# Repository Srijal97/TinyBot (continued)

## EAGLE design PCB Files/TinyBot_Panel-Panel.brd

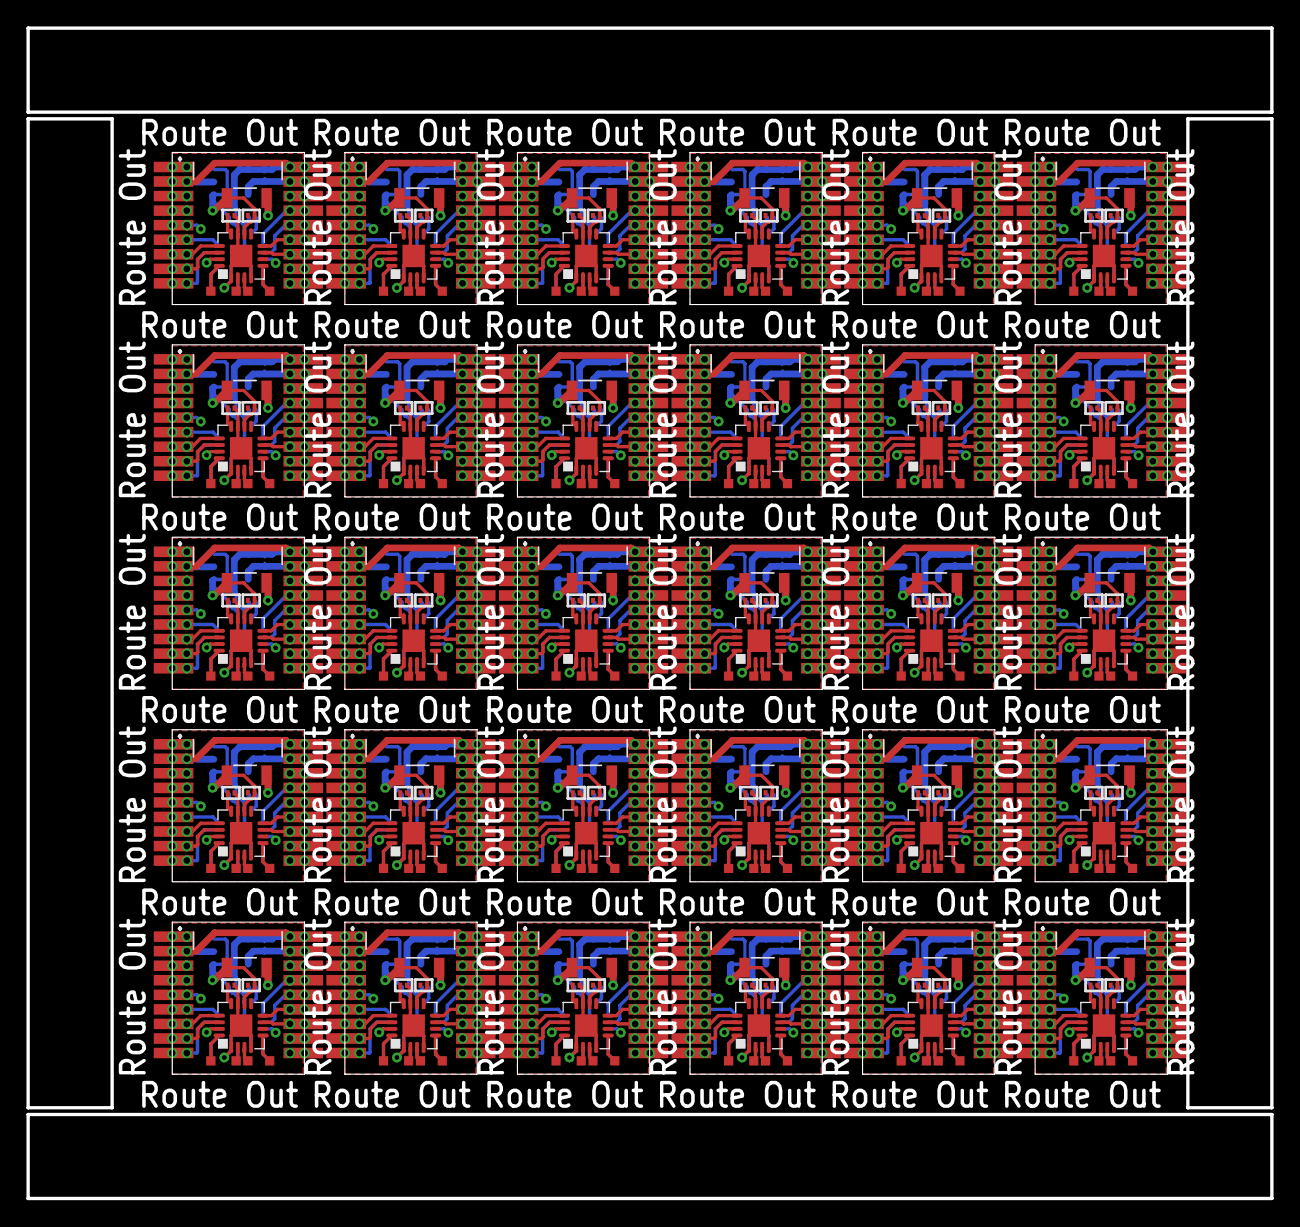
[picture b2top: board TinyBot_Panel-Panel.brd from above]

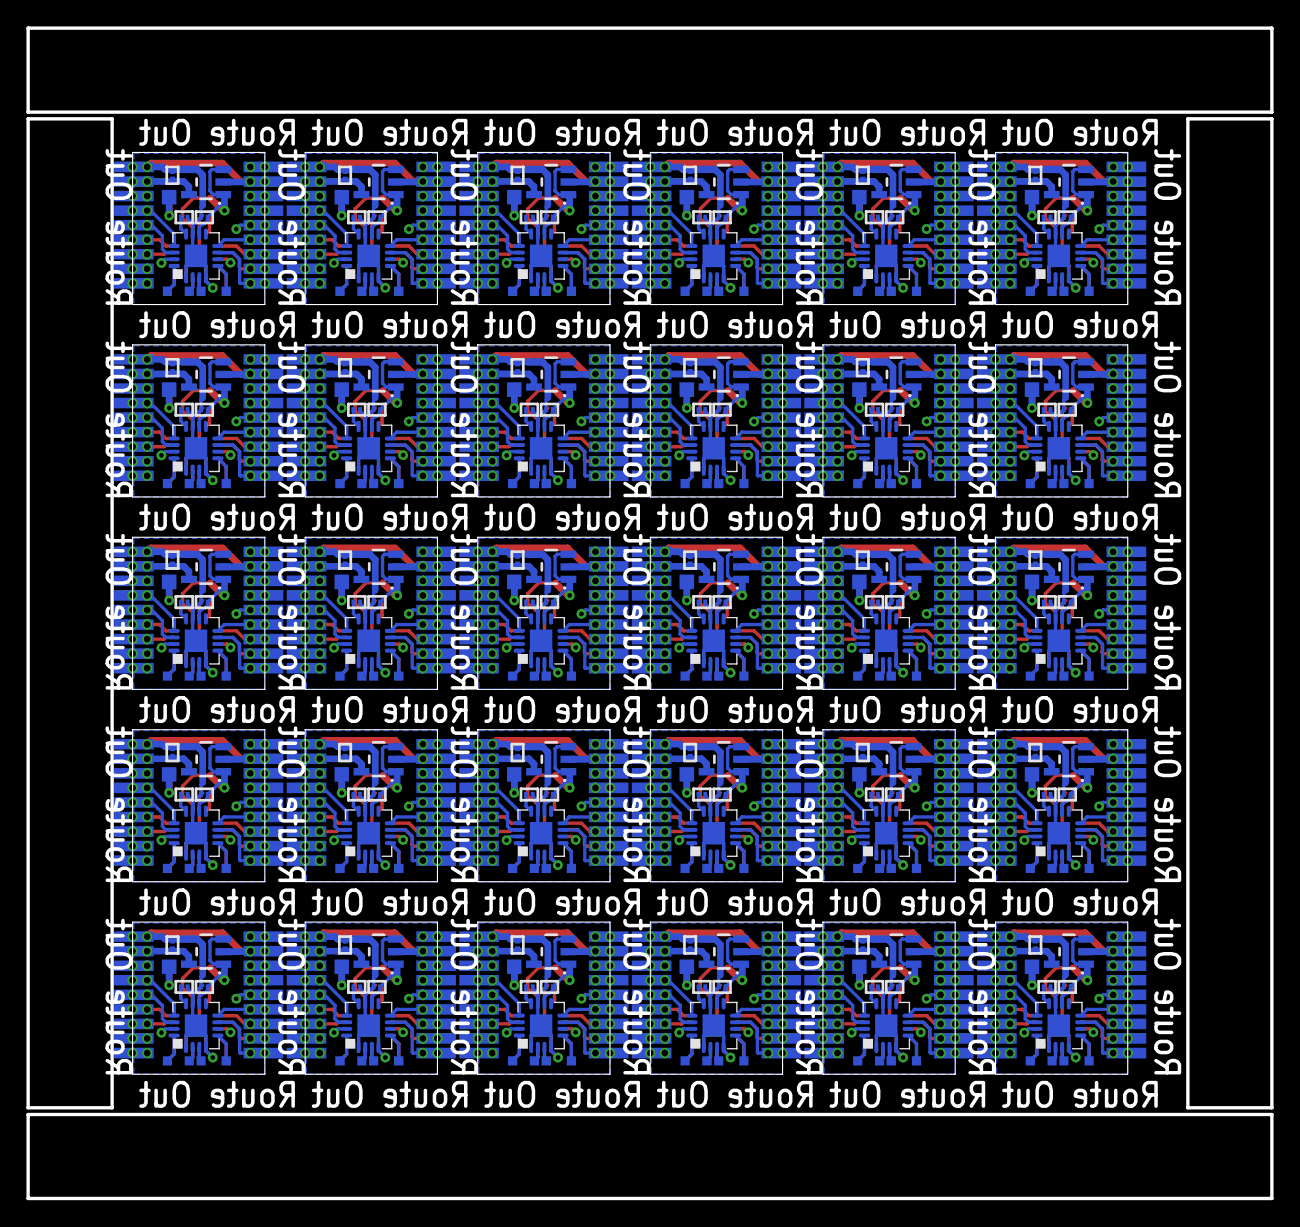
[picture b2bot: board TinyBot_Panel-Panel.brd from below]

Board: 2 copper layers, 94.0 x 88.5 mm, 570 parts (300 on the bottom side), 690 nets.

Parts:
C1, C2, C3, C4, C5, C6, C7, C8, C9, C10, C11, C12, C13, C14, C15, C16, C17, C18, C19, C20, C21, C22, C23, C24, C25, C26, C27, C28, C29, C30, C31, C32, C33, C34, C35, C36, C37, C38, C39, C40, C41, C42, C43, C44, C45, C46, C47, C48, C49, C50, C51, C52, C53, C54, C55, C56, C57, C58, C59, C60, C61, C62, C63, C64, C65, C66, C67, C68, C69, C70, C71, C72, C73, C74, C75, C76, C77, C78, C79, C80, C81, C82, C83, C84, C85, C86, C87, C88, C89, C90, C91, C92, C93, C94, C95, C96, C97, C98, C99, C100, C101, C102, C103, C104, C105, C106, C107, C108, C109, C110, C111, C112, C113, C114, C115, C116, C117, C118, C119, C120, C121, C122, C123, C124, C125, C126, C127, C128, C129, C130, C131, C132, C133, C134, C135, C136, C137, C138, C139, C140, C141, C142, C143, C144, C145, C146, C147, C148, C149, C150: C0201
LIPO_IN, LIPO_IN1, LIPO_IN2, LIPO_IN3, LIPO_IN4, LIPO_IN5, LIPO_IN6, LIPO_IN7, LIPO_IN8, LIPO_IN9, LIPO_IN10, LIPO_IN11, LIPO_IN12, LIPO_IN13, LIPO_IN14, LIPO_IN15, LIPO_IN16, LIPO_IN17, LIPO_IN18, LIPO_IN19, LIPO_IN20, LIPO_IN21, LIPO_IN22, LIPO_IN23, LIPO_IN24, LIPO_IN25, LIPO_IN26, LIPO_IN27, LIPO_IN28, LIPO_IN29: TPTP11SQ; TP11SQ
TP1, TP2, TP3, TP4, TP5, TP6, TP7, TP8, TP9, TP10, TP11, TP12, TP13, TP14, TP15, TP16, TP17, TP18, TP19, TP20, TP21, TP22, TP23, TP24, TP25, TP26, TP27, TP28, TP29, TP30, TP31, TP32, TP33, TP34, TP35, TP36, TP37, TP38, TP39, TP40, TP41, TP42, TP43, TP44, TP45, TP46, TP47, TP48, TP49, TP50, TP51, TP52, TP53, TP54, TP55, TP56, TP57, TP58, TP59, TP60, TP61, TP62, TP63, TP64, TP65, TP66, TP67, TP68, TP69, TP70, TP71, TP72, TP73, TP74, TP75, TP76, TP77, TP78, TP79, TP80, TP81, TP82, TP83, TP84, TP85, TP86, TP87, TP88, TP89, TP90, TP91, TP92, TP93, TP94, TP95, TP96, TP97, TP98, TP99, TP100, TP101, TP102, TP103, TP104, TP105, TP106, TP107, TP108, TP109, TP110, TP111, TP112, TP113, TP114, TP115, TP116, TP117, TP118, TP119, TP120, TP121, TP122, TP123, TP124, TP125, TP126, TP127, TP128, TP129, TP130, TP131, TP132, TP133, TP134, TP135, TP136, TP137, TP138, TP139, TP140, TP141, TP142, TP143, TP144, TP145, TP146, TP147, TP148, TP149, TP150, TP151, TP152, TP153, TP154, TP155, TP156, TP157, TP158, TP159, TP160, TP161, TP162, TP163, TP164, TP165, TP166, TP167, TP168, TP169, TP170, TP171, TP172, TP173, TP174, TP175, TP176, TP177, TP178, TP179, TP180, TP181, TP182, TP183, TP184, TP185, TP186, TP187, TP188, TP189, TP190, TP191, TP192, TP193, TP194, TP195, TP196, TP197, TP198, TP199, TP200, TP201, TP202, TP203, TP204, TP205, TP206, TP207, TP208, TP209, TP210, TP211, TP212, TP213, TP214, TP215, TP216, TP217, TP218, TP219, TP220, TP221, TP222, TP223, TP224, TP225, TP226, TP227, TP228, TP229, TP230, TP231, TP232, TP233, TP234, TP235, TP236, TP237, TP238, TP239, TP240: TPTP07SQ; TP07SQ
U$1, U$2, U$9, U$15, U$21, U$26, U$31, U$36, U$41, U$46, U$51, U$56, U$61, U$66, U$71, U$76, U$81, U$86, U$91, U$96, U$101, U$106, U$111, U$116, U$121, U$126, U$131, U$136, U$141, U$146: ESP01F
U$3, U$5, U$10, U$17, U$22, U$27, U$32, U$37, U$42, U$47, U$52, U$57, U$62, U$67, U$72, U$77, U$82, U$87, U$92, U$97, U$102, U$107, U$112, U$117, U$122, U$127, U$132, U$137, U$142, U$147: TLV755P; SOT23-5
U$4, U$8, U$14, U$20, U$25, U$30, U$35, U$40, U$45, U$50, U$55, U$60, U$65, U$70, U$75, U$80, U$85, U$90, U$95, U$100, U$105, U$110, U$115, U$120, U$125, U$130, U$135, U$140, U$145, U$150: MSK-12C02_SMD_SPDT_SWITCH_NOCLIP; MSK-12C02_NOCLIP
U$6, U$7, U$11, U$12, U$13, U$16, U$18, U$19, U$23, U$24, U$28, U$29, U$33, U$34, U$38, U$39, U$43, U$44, U$48, U$49, U$53, U$54, U$58, U$59, U$63, U$64, U$68, U$69, U$73, U$74, U$78, U$79, U$83, U$84, U$88, U$89, U$93, U$94, U$98, U$99, U$103, U$104, U$108, U$109, U$113, U$114, U$118, U$119, U$123, U$124, U$128, U$129, U$133, U$134, U$138, U$139, U$143, U$144, U$148, U$149: DRV8833C; QFN16

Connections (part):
3V1: C10.1, U$2.17, U$2.26, U$2.44, U$2.71, U$3.5
3V2: C15.1, U$9.17, U$9.26, U$9.44, U$9.71, U$10.5
3V3: C5.1, U$1.17, U$1.26, U$1.44, U$1.71, U$5.5
3V4: C20.1, U$15.17, U$15.26, U$15.44, U$15.71, U$17.5
3V5: C25.1, U$21.17, U$21.26, U$21.44, U$21.71, U$22.5
3V6: C30.1, U$26.17, U$26.26, U$26.44, U$26.71, U$27.5
3V7: C35.1, U$31.17, U$31.26, U$31.44, U$31.71, U$32.5
3V8: C40.1, U$36.17, U$36.26, U$36.44, U$36.71, U$37.5
3V9: C45.1, U$41.17, U$41.26, U$41.44, U$41.71, U$42.5
3V10: C50.1, U$46.17, U$46.26, U$46.44, U$46.71, U$47.5
3V11: C55.1, U$51.17, U$51.26, U$51.44, U$51.71, U$52.5
3V12: C60.1, U$56.17, U$56.26, U$56.44, U$56.71, U$57.5
3V13: C65.1, U$61.17, U$61.26, U$61.44, U$61.71, U$62.5
3V14: C70.1, U$66.17, U$66.26, U$66.44, U$66.71, U$67.5
3V15: C75.1, U$71.17, U$71.26, U$71.44, U$71.71, U$72.5
3V16: C80.1, U$76.17, U$76.26, U$76.44, U$76.71, U$77.5
3V17: C85.1, U$81.17, U$81.26, U$81.44, U$81.71, U$82.5
3V18: C90.1, U$86.17, U$86.26, U$86.44, U$86.71, U$87.5
3V19: C95.1, U$91.17, U$91.26, U$91.44, U$91.71, U$92.5
3V20: C100.1, U$96.17, U$96.26, U$96.44, U$96.71, U$97.5
3V21: C105.1, U$101.17, U$101.26, U$101.44, U$101.71, U$102.5
3V22: C110.1, U$106.17, U$106.26, U$106.44, U$106.71, U$107.5
3V23: C115.1, U$111.17, U$111.26, U$111.44, U$111.71, U$112.5
3V24: C120.1, U$116.17, U$116.26, U$116.44, U$116.71, U$117.5
3V25: C125.1, U$121.17, U$121.26, U$121.44, U$121.71, U$122.5
3V26: C130.1, U$126.17, U$126.26, U$126.44, U$126.71, U$127.5
3V27: C135.1, U$131.17, U$131.26, U$131.44, U$131.71, U$132.5
3V28: C140.1, U$136.17, U$136.26, U$136.44, U$136.71, U$137.5
3V29: C145.1, U$141.17, U$141.26, U$141.44, U$141.71, U$142.5
3V30: C150.1, U$146.17, U$146.26, U$146.44, U$146.71, U$147.5
AIN1_A: U$1.2, U$1.29, U$1.47, U$1.56, U$11.14
AIN1_A1: U$2.2, U$2.29, U$2.47, U$2.56, U$6.14
AIN1_A2: U$9.2, U$9.29, U$9.47, U$9.56, U$12.14
AIN1_A3: U$15.2, U$15.29, U$15.47, U$15.56, U$18.14
AIN1_A4: U$21.2, U$21.29, U$21.47, U$21.56, U$23.14
AIN1_A5: U$26.2, U$26.29, U$26.47, U$26.56, U$28.14
AIN1_A6: U$31.2, U$31.29, U$31.47, U$31.56, U$33.14
AIN1_A7: U$36.2, U$36.29, U$36.47, U$36.56, U$38.14
AIN1_A8: U$41.2, U$41.29, U$41.47, U$41.56, U$43.14
AIN1_A9: U$46.2, U$46.29, U$46.47, U$46.56, U$48.14
AIN1_A10: U$51.2, U$51.29, U$51.47, U$51.56, U$53.14
AIN1_A11: U$56.2, U$56.29, U$56.47, U$56.56, U$58.14
AIN1_A12: U$61.2, U$61.29, U$61.47, U$61.56, U$63.14
AIN1_A13: U$66.2, U$66.29, U$66.47, U$66.56, U$68.14
AIN1_A14: U$71.2, U$71.29, U$71.47, U$71.56, U$73.14
AIN1_A15: U$76.2, U$76.29, U$76.47, U$76.56, U$78.14
AIN1_A16: U$81.2, U$81.29, U$81.47, U$81.56, U$83.14
AIN1_A17: U$86.2, U$86.29, U$86.47, U$86.56, U$88.14
AIN1_A18: U$91.2, U$91.29, U$91.47, U$91.56, U$93.14
AIN1_A19: U$96.2, U$96.29, U$96.47, U$96.56, U$98.14
AIN1_A20: U$101.2, U$101.29, U$101.47, U$101.56, U$103.14
AIN1_A21: U$106.2, U$106.29, U$106.47, U$106.56, U$108.14
AIN1_A22: U$111.2, U$111.29, U$111.47, U$111.56, U$113.14
AIN1_A23: U$116.2, U$116.29, U$116.47, U$116.56, U$118.14
AIN1_A24: U$121.2, U$121.29, U$121.47, U$121.56, U$123.14
AIN1_A25: U$126.2, U$126.29, U$126.47, U$126.56, U$128.14
AIN1_A26: U$131.2, U$131.29, U$131.47, U$131.56, U$133.14
AIN1_A27: U$136.2, U$136.29, U$136.47, U$136.56, U$138.14
AIN1_A28: U$141.2, U$141.29, U$141.47, U$141.56, U$143.14
AIN1_A29: U$146.2, U$146.29, U$146.47, U$146.56, U$148.14
AIN1_B: U$1.14, U$1.23, U$1.41, U$1.68, U$16.14
AIN1_B1: U$2.14, U$2.23, U$2.41, U$2.68, U$7.14
AIN1_B2: U$9.14, U$9.23, U$9.41, U$9.68, U$13.14
AIN1_B3: U$15.14, U$15.23, U$15.41, U$15.68, U$19.14
AIN1_B4: U$21.14, U$21.23, U$21.41, U$21.68, U$24.14
AIN1_B5: U$26.14, U$26.23, U$26.41, U$26.68, U$29.14
AIN1_B6: U$31.14, U$31.23, U$31.41, U$31.68, U$34.14
AIN1_B7: U$36.14, U$36.23, U$36.41, U$36.68, U$39.14
AIN1_B8: U$41.14, U$41.23, U$41.41, U$41.68, U$44.14
AIN1_B9: U$46.14, U$46.23, U$46.41, U$46.68, U$49.14
AIN1_B10: U$51.14, U$51.23, U$51.41, U$51.68, U$54.14
AIN1_B11: U$56.14, U$56.23, U$56.41, U$56.68, U$59.14
AIN1_B12: U$61.14, U$61.23, U$61.41, U$61.68, U$64.14
AIN1_B13: U$66.14, U$66.23, U$66.41, U$66.68, U$69.14
AIN1_B14: U$71.14, U$71.23, U$71.41, U$71.68, U$74.14
AIN1_B15: U$76.14, U$76.23, U$76.41, U$76.68, U$79.14
AIN1_B16: U$81.14, U$81.23, U$81.41, U$81.68, U$84.14
AIN1_B17: U$86.14, U$86.23, U$86.41, U$86.68, U$89.14
AIN1_B18: U$91.14, U$91.23, U$91.41, U$91.68, U$94.14
AIN1_B19: U$96.14, U$96.23, U$96.41, U$96.68, U$99.14
AIN1_B20: U$101.14, U$101.23, U$101.41, U$101.68, U$104.14
AIN1_B21: U$106.14, U$106.23, U$106.41, U$106.68, U$109.14
AIN1_B22: U$111.14, U$111.23, U$111.41, U$111.68, U$114.14
AIN1_B23: U$116.14, U$116.23, U$116.41, U$116.68, U$119.14
AIN1_B24: U$121.14, U$121.23, U$121.41, U$121.68, U$124.14
AIN1_B25: U$126.14, U$126.23, U$126.41, U$126.68, U$129.14
AIN1_B26: U$131.14, U$131.23, U$131.41, U$131.68, U$134.14
AIN1_B27: U$136.14, U$136.23, U$136.41, U$136.68, U$139.14
AIN1_B28: U$141.14, U$141.23, U$141.41, U$141.68, U$144.14
AIN1_B29: U$146.14, U$146.23, U$146.41, U$146.68, U$149.14
AIN2_A: U$1.3, U$1.30, U$1.48, U$1.57, U$11.13
AIN2_A1: U$2.3, U$2.30, U$2.48, U$2.57, U$6.13
AIN2_A2: U$9.3, U$9.30, U$9.48, U$9.57, U$12.13
AIN2_A3: U$15.3, U$15.30, U$15.48, U$15.57, U$18.13
AIN2_A4: U$21.3, U$21.30, U$21.48, U$21.57, U$23.13
AIN2_A5: U$26.3, U$26.30, U$26.48, U$26.57, U$28.13
AIN2_A6: U$31.3, U$31.30, U$31.48, U$31.57, U$33.13
AIN2_A7: U$36.3, U$36.30, U$36.48, U$36.57, U$38.13
AIN2_A8: U$41.3, U$41.30, U$41.48, U$41.57, U$43.13
AIN2_A9: U$46.3, U$46.30, U$46.48, U$46.57, U$48.13
AIN2_A10: U$51.3, U$51.30, U$51.48, U$51.57, U$53.13
AIN2_A11: U$56.3, U$56.30, U$56.48, U$56.57, U$58.13
AIN2_A12: U$61.3, U$61.30, U$61.48, U$61.57, U$63.13
AIN2_A13: U$66.3, U$66.30, U$66.48, U$66.57, U$68.13
AIN2_A14: U$71.3, U$71.30, U$71.48, U$71.57, U$73.13
AIN2_A15: U$76.3, U$76.30, U$76.48, U$76.57, U$78.13
AIN2_A16: U$81.3, U$81.30, U$81.48, U$81.57, U$83.13
AIN2_A17: U$86.3, U$86.30, U$86.48, U$86.57, U$88.13
AIN2_A18: U$91.3, U$91.30, U$91.48, U$91.57, U$93.13
AIN2_A19: U$96.3, U$96.30, U$96.48, U$96.57, U$98.13
AIN2_A20: U$101.3, U$101.30, U$101.48, U$101.57, U$103.13
AIN2_A21: U$106.3, U$106.30, U$106.48, U$106.57, U$108.13
AIN2_A22: U$111.3, U$111.30, U$111.48, U$111.57, U$113.13
AIN2_A23: U$116.3, U$116.30, U$116.48, U$116.57, U$118.13
AIN2_A24: U$121.3, U$121.30, U$121.48, U$121.57, U$123.13
AIN2_A25: U$126.3, U$126.30, U$126.48, U$126.57, U$128.13
AIN2_A26: U$131.3, U$131.30, U$131.48, U$131.57, U$133.13
AIN2_A27: U$136.3, U$136.30, U$136.48, U$136.57, U$138.13
AIN2_A28: U$141.3, U$141.30, U$141.48, U$141.57, U$143.13
AIN2_A29: U$146.3, U$146.30, U$146.48, U$146.57, U$148.13
AIN2_B: U$1.15, U$1.24, U$1.42, U$1.69, U$16.13
AIN2_B1: U$2.15, U$2.24, U$2.42, U$2.69, U$7.13
AIN2_B2: U$9.15, U$9.24, U$9.42, U$9.69, U$13.13
AIN2_B3: U$15.15, U$15.24, U$15.42, U$15.69, U$19.13
AIN2_B4: U$21.15, U$21.24, U$21.42, U$21.69, U$24.13
AIN2_B5: U$26.15, U$26.24, U$26.42, U$26.69, U$29.13
AIN2_B6: U$31.15, U$31.24, U$31.42, U$31.69, U$34.13
AIN2_B7: U$36.15, U$36.24, U$36.42, U$36.69, U$39.13
AIN2_B8: U$41.15, U$41.24, U$41.42, U$41.69, U$44.13
AIN2_B9: U$46.15, U$46.24, U$46.42, U$46.69, U$49.13
AIN2_B10: U$51.15, U$51.24, U$51.42, U$51.69, U$54.13
AIN2_B11: U$56.15, U$56.24, U$56.42, U$56.69, U$59.13
AIN2_B12: U$61.15, U$61.24, U$61.42, U$61.69, U$64.13
AIN2_B13: U$66.15, U$66.24, U$66.42, U$66.69, U$69.13
AIN2_B14: U$71.15, U$71.24, U$71.42, U$71.69, U$74.13
AIN2_B15: U$76.15, U$76.24, U$76.42, U$76.69, U$79.13
AIN2_B16: U$81.15, U$81.24, U$81.42, U$81.69, U$84.13
AIN2_B17: U$86.15, U$86.24, U$86.42, U$86.69, U$89.13
AIN2_B18: U$91.15, U$91.24, U$91.42, U$91.69, U$94.13
AIN2_B19: U$96.15, U$96.24, U$96.42, U$96.69, U$99.13
AIN2_B20: U$101.15, U$101.24, U$101.42, U$101.69, U$104.13
AIN2_B21: U$106.15, U$106.24, U$106.42, U$106.69, U$109.13
AIN2_B22: U$111.15, U$111.24, U$111.42, U$111.69, U$114.13
AIN2_B23: U$116.15, U$116.24, U$116.42, U$116.69, U$119.13
AIN2_B24: U$121.15, U$121.24, U$121.42, U$121.69, U$124.13
AIN2_B25: U$126.15, U$126.24, U$126.42, U$126.69, U$129.13
AIN2_B26: U$131.15, U$131.24, U$131.42, U$131.69, U$134.13
AIN2_B27: U$136.15, U$136.24, U$136.42, U$136.69, U$139.13
AIN2_B28: U$141.15, U$141.24, U$141.42, U$141.69, U$144.13
AIN2_B29: U$146.15, U$146.24, U$146.42, U$146.69, U$149.13
AOUT1_A: TP1.TP, U$11.16
AOUT1_A1: TP10.TP, U$6.16
AOUT1_A2: TP18.TP, U$12.16
AOUT1_A3: TP26.TP, U$18.16
AOUT1_A4: TP34.TP, U$23.16
AOUT1_A5: TP42.TP, U$28.16
AOUT1_A6: TP50.TP, U$33.16
AOUT1_A7: TP58.TP, U$38.16
AOUT1_A8: TP66.TP, U$43.16
AOUT1_A9: TP74.TP, U$48.16
AOUT1_A10: TP82.TP, U$53.16
AOUT1_A11: TP90.TP, U$58.16
AOUT1_A12: TP98.TP, U$63.16
AOUT1_A13: TP106.TP, U$68.16
AOUT1_A14: TP114.TP, U$73.16
AOUT1_A15: TP122.TP, U$78.16
AOUT1_A16: TP130.TP, U$83.16
AOUT1_A17: TP138.TP, U$88.16
AOUT1_A18: TP146.TP, U$93.16
AOUT1_A19: TP154.TP, U$98.16
AOUT1_A20: TP162.TP, U$103.16
AOUT1_A21: TP170.TP, U$108.16
AOUT1_A22: TP178.TP, U$113.16
AOUT1_A23: TP186.TP, U$118.16
AOUT1_A24: TP194.TP, U$123.16
AOUT1_A25: TP202.TP, U$128.16
AOUT1_A26: TP210.TP, U$133.16
AOUT1_A27: TP218.TP, U$138.16
AOUT1_A28: TP226.TP, U$143.16
AOUT1_A29: TP234.TP, U$148.16
AOUT1_B: TP5.TP, U$16.16
AOUT1_B1: TP13.TP, U$7.16
AOUT1_B2: TP21.TP, U$13.16
AOUT1_B3: TP29.TP, U$19.16
AOUT1_B4: TP37.TP, U$24.16
AOUT1_B5: TP45.TP, U$29.16
AOUT1_B6: TP53.TP, U$34.16
AOUT1_B7: TP61.TP, U$39.16
AOUT1_B8: TP69.TP, U$44.16
AOUT1_B9: TP77.TP, U$49.16
AOUT1_B10: TP85.TP, U$54.16
AOUT1_B11: TP93.TP, U$59.16
AOUT1_B12: TP101.TP, U$64.16
AOUT1_B13: TP109.TP, U$69.16
AOUT1_B14: TP117.TP, U$74.16
AOUT1_B15: TP125.TP, U$79.16
AOUT1_B16: TP133.TP, U$84.16
AOUT1_B17: TP141.TP, U$89.16
AOUT1_B18: TP149.TP, U$94.16
AOUT1_B19: TP157.TP, U$99.16
AOUT1_B20: TP165.TP, U$104.16
AOUT1_B21: TP173.TP, U$109.16
AOUT1_B22: TP181.TP, U$114.16
AOUT1_B23: TP189.TP, U$119.16
AOUT1_B24: TP197.TP, U$124.16
AOUT1_B25: TP205.TP, U$129.16
AOUT1_B26: TP213.TP, U$134.16
AOUT1_B27: TP221.TP, U$139.16
AOUT1_B28: TP229.TP, U$144.16
AOUT1_B29: TP237.TP, U$149.16
AOUT2_A: TP2.TP, U$11.2
AOUT2_A1: TP9.TP, U$6.2
AOUT2_A2: TP17.TP, U$12.2
AOUT2_A3: TP25.TP, U$18.2
AOUT2_A4: TP33.TP, U$23.2
AOUT2_A5: TP41.TP, U$28.2
AOUT2_A6: TP49.TP, U$33.2
AOUT2_A7: TP57.TP, U$38.2
AOUT2_A8: TP65.TP, U$43.2
AOUT2_A9: TP73.TP, U$48.2
AOUT2_A10: TP81.TP, U$53.2
AOUT2_A11: TP89.TP, U$58.2
AOUT2_A12: TP97.TP, U$63.2
AOUT2_A13: TP105.TP, U$68.2
AOUT2_A14: TP113.TP, U$73.2
AOUT2_A15: TP121.TP, U$78.2
AOUT2_A16: TP129.TP, U$83.2
AOUT2_A17: TP137.TP, U$88.2
AOUT2_A18: TP145.TP, U$93.2
AOUT2_A19: TP153.TP, U$98.2
AOUT2_A20: TP161.TP, U$103.2
AOUT2_A21: TP169.TP, U$108.2
AOUT2_A22: TP177.TP, U$113.2
AOUT2_A23: TP185.TP, U$118.2
AOUT2_A24: TP193.TP, U$123.2
AOUT2_A25: TP201.TP, U$128.2
AOUT2_A26: TP209.TP, U$133.2
AOUT2_A27: TP217.TP, U$138.2
AOUT2_A28: TP225.TP, U$143.2
AOUT2_A29: TP233.TP, U$148.2
AOUT2_B: TP6.TP, U$16.2
AOUT2_B1: TP14.TP, U$7.2
AOUT2_B2: TP22.TP, U$13.2
AOUT2_B3: TP30.TP, U$19.2
AOUT2_B4: TP38.TP, U$24.2
AOUT2_B5: TP46.TP, U$29.2
AOUT2_B6: TP54.TP, U$34.2
AOUT2_B7: TP62.TP, U$39.2
AOUT2_B8: TP70.TP, U$44.2
AOUT2_B9: TP78.TP, U$49.2
AOUT2_B10: TP86.TP, U$54.2
AOUT2_B11: TP94.TP, U$59.2
AOUT2_B12: TP102.TP, U$64.2
AOUT2_B13: TP110.TP, U$69.2
AOUT2_B14: TP118.TP, U$74.2
AOUT2_B15: TP126.TP, U$79.2
AOUT2_B16: TP134.TP, U$84.2
AOUT2_B17: TP142.TP, U$89.2
AOUT2_B18: TP150.TP, U$94.2
AOUT2_B19: TP158.TP, U$99.2
AOUT2_B20: TP166.TP, U$104.2
AOUT2_B21: TP174.TP, U$109.2
AOUT2_B22: TP182.TP, U$114.2
AOUT2_B23: TP190.TP, U$119.2
AOUT2_B24: TP198.TP, U$124.2
AOUT2_B25: TP206.TP, U$129.2
AOUT2_B26: TP214.TP, U$134.2
AOUT2_B27: TP222.TP, U$139.2
AOUT2_B28: TP230.TP, U$144.2
AOUT2_B29: TP238.TP, U$149.2
BIN1_A: U$1.12, U$1.21, U$1.39, U$1.66, U$11.7
BIN1_A1: U$2.12, U$2.21, U$2.39, U$2.66, U$6.7
BIN1_A2: U$9.12, U$9.21, U$9.39, U$9.66, U$12.7
BIN1_A3: U$15.12, U$15.21, U$15.39, U$15.66, U$18.7
BIN1_A4: U$21.12, U$21.21, U$21.39, U$21.66, U$23.7
BIN1_A5: U$26.12, U$26.21, U$26.39, U$26.66, U$28.7
BIN1_A6: U$31.12, U$31.21, U$31.39, U$31.66, U$33.7
BIN1_A7: U$36.12, U$36.21, U$36.39, U$36.66, U$38.7
BIN1_A8: U$41.12, U$41.21, U$41.39, U$41.66, U$43.7
BIN1_A9: U$46.12, U$46.21, U$46.39, U$46.66, U$48.7
BIN1_A10: U$51.12, U$51.21, U$51.39, U$51.66, U$53.7
BIN1_A11: U$56.12, U$56.21, U$56.39, U$56.66, U$58.7
BIN1_A12: U$61.12, U$61.21, U$61.39, U$61.66, U$63.7
BIN1_A13: U$66.12, U$66.21, U$66.39, U$66.66, U$68.7
BIN1_A14: U$71.12, U$71.21, U$71.39, U$71.66, U$73.7
BIN1_A15: U$76.12, U$76.21, U$76.39, U$76.66, U$78.7
BIN1_A16: U$81.12, U$81.21, U$81.39, U$81.66, U$83.7
BIN1_A17: U$86.12, U$86.21, U$86.39, U$86.66, U$88.7
BIN1_A18: U$91.12, U$91.21, U$91.39, U$91.66, U$93.7
BIN1_A19: U$96.12, U$96.21, U$96.39, U$96.66, U$98.7
BIN1_A20: U$101.12, U$101.21, U$101.39, U$101.66, U$103.7
BIN1_A21: U$106.12, U$106.21, U$106.39, U$106.66, U$108.7
BIN1_A22: U$111.12, U$111.21, U$111.39, U$111.66, U$113.7
BIN1_A23: U$116.12, U$116.21, U$116.39, U$116.66, U$118.7
BIN1_A24: U$121.12, U$121.21, U$121.39, U$121.66, U$123.7
BIN1_A25: U$126.12, U$126.21, U$126.39, U$126.66, U$128.7
BIN1_A26: U$131.12, U$131.21, U$131.39, U$131.66, U$133.7
BIN1_A27: U$136.12, U$136.21, U$136.39, U$136.66, U$138.7
BIN1_A28: U$141.12, U$141.21, U$141.39, U$141.66, U$143.7
BIN1_A29: U$146.12, U$146.21, U$146.39, U$146.66, U$148.7
BIN1_B: U$1.1, U$1.28, U$1.46, U$1.55, U$16.7
BIN1_B1: U$2.1, U$2.28, U$2.46, U$2.55, U$7.7
BIN1_B2: U$9.1, U$9.28, U$9.46, U$9.55, U$13.7
BIN1_B3: U$15.1, U$15.28, U$15.46, U$15.55, U$19.7
BIN1_B4: U$21.1, U$21.28, U$21.46, U$21.55, U$24.7
BIN1_B5: U$26.1, U$26.28, U$26.46, U$26.55, U$29.7
BIN1_B6: U$31.1, U$31.28, U$31.46, U$31.55, U$34.7
BIN1_B7: U$36.1, U$36.28, U$36.46, U$36.55, U$39.7
BIN1_B8: U$41.1, U$41.28, U$41.46, U$41.55, U$44.7
BIN1_B9: U$46.1, U$46.28, U$46.46, U$46.55, U$49.7
BIN1_B10: U$51.1, U$51.28, U$51.46, U$51.55, U$54.7
BIN1_B11: U$56.1, U$56.28, U$56.46, U$56.55, U$59.7
BIN1_B12: U$61.1, U$61.28, U$61.46, U$61.55, U$64.7
BIN1_B13: U$66.1, U$66.28, U$66.46, U$66.55, U$69.7
BIN1_B14: U$71.1, U$71.28, U$71.46, U$71.55, U$74.7
BIN1_B15: U$76.1, U$76.28, U$76.46, U$76.55, U$79.7
BIN1_B16: U$81.1, U$81.28, U$81.46, U$81.55, U$84.7
BIN1_B17: U$86.1, U$86.28, U$86.46, U$86.55, U$89.7
BIN1_B18: U$91.1, U$91.28, U$91.46, U$91.55, U$94.7
BIN1_B19: U$96.1, U$96.28, U$96.46, U$96.55, U$99.7
BIN1_B20: U$101.1, U$101.28, U$101.46, U$101.55, U$104.7
BIN1_B21: U$106.1, U$106.28, U$106.46, U$106.55, U$109.7
BIN1_B22: U$111.1, U$111.28, U$111.46, U$111.55, U$114.7
BIN1_B23: U$116.1, U$116.28, U$116.46, U$116.55, U$119.7
BIN1_B24: U$121.1, U$121.28, U$121.46, U$121.55, U$124.7
BIN1_B25: U$126.1, U$126.28, U$126.46, U$126.55, U$129.7
BIN1_B26: U$131.1, U$131.28, U$131.46, U$131.55, U$134.7
BIN1_B27: U$136.1, U$136.28, U$136.46, U$136.55, U$139.7
BIN1_B28: U$141.1, U$141.28, U$141.46, U$141.55, U$144.7
BIN1_B29: U$146.1, U$146.28, U$146.46, U$146.55, U$149.7
BIN2_A: U$1.13, U$1.22, U$1.40, U$1.67, U$11.8
BIN2_A1: U$2.13, U$2.22, U$2.40, U$2.67, U$6.8
BIN2_A2: U$9.13, U$9.22, U$9.40, U$9.67, U$12.8
BIN2_A3: U$15.13, U$15.22, U$15.40, U$15.67, U$18.8
BIN2_A4: U$21.13, U$21.22, U$21.40, U$21.67, U$23.8
BIN2_A5: U$26.13, U$26.22, U$26.40, U$26.67, U$28.8
BIN2_A6: U$31.13, U$31.22, U$31.40, U$31.67, U$33.8
BIN2_A7: U$36.13, U$36.22, U$36.40, U$36.67, U$38.8
BIN2_A8: U$41.13, U$41.22, U$41.40, U$41.67, U$43.8
BIN2_A9: U$46.13, U$46.22, U$46.40, U$46.67, U$48.8
BIN2_A10: U$51.13, U$51.22, U$51.40, U$51.67, U$53.8
BIN2_A11: U$56.13, U$56.22, U$56.40, U$56.67, U$58.8
BIN2_A12: U$61.13, U$61.22, U$61.40, U$61.67, U$63.8
BIN2_A13: U$66.13, U$66.22, U$66.40, U$66.67, U$68.8
BIN2_A14: U$71.13, U$71.22, U$71.40, U$71.67, U$73.8
BIN2_A15: U$76.13, U$76.22, U$76.40, U$76.67, U$78.8
BIN2_A16: U$81.13, U$81.22, U$81.40, U$81.67, U$83.8
BIN2_A17: U$86.13, U$86.22, U$86.40, U$86.67, U$88.8
BIN2_A18: U$91.13, U$91.22, U$91.40, U$91.67, U$93.8
BIN2_A19: U$96.13, U$96.22, U$96.40, U$96.67, U$98.8
BIN2_A20: U$101.13, U$101.22, U$101.40, U$101.67, U$103.8
BIN2_A21: U$106.13, U$106.22, U$106.40, U$106.67, U$108.8
BIN2_A22: U$111.13, U$111.22, U$111.40, U$111.67, U$113.8
BIN2_A23: U$116.13, U$116.22, U$116.40, U$116.67, U$118.8
BIN2_A24: U$121.13, U$121.22, U$121.40, U$121.67, U$123.8
BIN2_A25: U$126.13, U$126.22, U$126.40, U$126.67, U$128.8
BIN2_A26: U$131.13, U$131.22, U$131.40, U$131.67, U$133.8
BIN2_A27: U$136.13, U$136.22, U$136.40, U$136.67, U$138.8
BIN2_A28: U$141.13, U$141.22, U$141.40, U$141.67, U$143.8
BIN2_A29: U$146.13, U$146.22, U$146.40, U$146.67, U$148.8
BIN2_B: U$1.4, U$1.31, U$1.49, U$1.58, U$16.8
BIN2_B1: U$2.4, U$2.31, U$2.49, U$2.58, U$7.8
BIN2_B2: U$9.4, U$9.31, U$9.49, U$9.58, U$13.8
BIN2_B3: U$15.4, U$15.31, U$15.49, U$15.58, U$19.8
BIN2_B4: U$21.4, U$21.31, U$21.49, U$21.58, U$24.8
BIN2_B5: U$26.4, U$26.31, U$26.49, U$26.58, U$29.8
BIN2_B6: U$31.4, U$31.31, U$31.49, U$31.58, U$34.8
BIN2_B7: U$36.4, U$36.31, U$36.49, U$36.58, U$39.8
BIN2_B8: U$41.4, U$41.31, U$41.49, U$41.58, U$44.8
BIN2_B9: U$46.4, U$46.31, U$46.49, U$46.58, U$49.8
BIN2_B10: U$51.4, U$51.31, U$51.49, U$51.58, U$54.8
BIN2_B11: U$56.4, U$56.31, U$56.49, U$56.58, U$59.8
BIN2_B12: U$61.4, U$61.31, U$61.49, U$61.58, U$64.8
BIN2_B13: U$66.4, U$66.31, U$66.49, U$66.58, U$69.8
BIN2_B14: U$71.4, U$71.31, U$71.49, U$71.58, U$74.8
BIN2_B15: U$76.4, U$76.31, U$76.49, U$76.58, U$79.8
BIN2_B16: U$81.4, U$81.31, U$81.49, U$81.58, U$84.8
BIN2_B17: U$86.4, U$86.31, U$86.49, U$86.58, U$89.8
BIN2_B18: U$91.4, U$91.31, U$91.49, U$91.58, U$94.8
BIN2_B19: U$96.4, U$96.31, U$96.49, U$96.58, U$99.8
BIN2_B20: U$101.4, U$101.31, U$101.49, U$101.58, U$104.8
BIN2_B21: U$106.4, U$106.31, U$106.49, U$106.58, U$109.8
BIN2_B22: U$111.4, U$111.31, U$111.49, U$111.58, U$114.8
BIN2_B23: U$116.4, U$116.31, U$116.49, U$116.58, U$119.8
BIN2_B24: U$121.4, U$121.31, U$121.49, U$121.58, U$124.8
BIN2_B25: U$126.4, U$126.31, U$126.49, U$126.58, U$129.8
BIN2_B26: U$131.4, U$131.31, U$131.49, U$131.58, U$134.8
BIN2_B27: U$136.4, U$136.31, U$136.49, U$136.58, U$139.8
BIN2_B28: U$141.4, U$141.31, U$141.49, U$141.58, U$144.8
BIN2_B29: U$146.4, U$146.31, U$146.49, U$146.58, U$149.8
BOUT1_A: TP3.TP, U$11.5
BOUT1_A1: TP11.TP, U$6.5
BOUT1_A2: TP19.TP, U$12.5
BOUT1_A3: TP27.TP, U$18.5
BOUT1_A4: TP35.TP, U$23.5
BOUT1_A5: TP43.TP, U$28.5
BOUT1_A6: TP51.TP, U$33.5
BOUT1_A7: TP59.TP, U$38.5
BOUT1_A8: TP67.TP, U$43.5
BOUT1_A9: TP75.TP, U$48.5
BOUT1_A10: TP83.TP, U$53.5
BOUT1_A11: TP91.TP, U$58.5
BOUT1_A12: TP99.TP, U$63.5
BOUT1_A13: TP107.TP, U$68.5
BOUT1_A14: TP115.TP, U$73.5
BOUT1_A15: TP123.TP, U$78.5
BOUT1_A16: TP131.TP, U$83.5
BOUT1_A17: TP139.TP, U$88.5
BOUT1_A18: TP147.TP, U$93.5
BOUT1_A19: TP155.TP, U$98.5
BOUT1_A20: TP163.TP, U$103.5
BOUT1_A21: TP171.TP, U$108.5
BOUT1_A22: TP179.TP, U$113.5
BOUT1_A23: TP187.TP, U$118.5
BOUT1_A24: TP195.TP, U$123.5
BOUT1_A25: TP203.TP, U$128.5
BOUT1_A26: TP211.TP, U$133.5
BOUT1_A27: TP219.TP, U$138.5
BOUT1_A28: TP227.TP, U$143.5
BOUT1_A29: TP235.TP, U$148.5
BOUT1_B: TP7.TP, U$16.5
BOUT1_B1: TP15.TP, U$7.5
BOUT1_B2: TP23.TP, U$13.5
BOUT1_B3: TP31.TP, U$19.5
BOUT1_B4: TP39.TP, U$24.5
BOUT1_B5: TP47.TP, U$29.5
BOUT1_B6: TP55.TP, U$34.5
BOUT1_B7: TP63.TP, U$39.5
BOUT1_B8: TP71.TP, U$44.5
BOUT1_B9: TP79.TP, U$49.5
BOUT1_B10: TP87.TP, U$54.5
BOUT1_B11: TP95.TP, U$59.5
BOUT1_B12: TP103.TP, U$64.5
BOUT1_B13: TP111.TP, U$69.5
BOUT1_B14: TP119.TP, U$74.5
BOUT1_B15: TP127.TP, U$79.5
BOUT1_B16: TP135.TP, U$84.5
BOUT1_B17: TP143.TP, U$89.5
BOUT1_B18: TP151.TP, U$94.5
BOUT1_B19: TP159.TP, U$99.5
BOUT1_B20: TP167.TP, U$104.5
BOUT1_B21: TP175.TP, U$109.5
BOUT1_B22: TP183.TP, U$114.5
BOUT1_B23: TP191.TP, U$119.5
BOUT1_B24: TP199.TP, U$124.5
BOUT1_B25: TP207.TP, U$129.5
BOUT1_B26: TP215.TP, U$134.5
BOUT1_B27: TP223.TP, U$139.5
BOUT1_B28: TP231.TP, U$144.5
BOUT1_B29: TP239.TP, U$149.5
BOUT2_A: TP4.TP, U$11.3
BOUT2_A1: TP12.TP, U$6.3
BOUT2_A2: TP20.TP, U$12.3
BOUT2_A3: TP28.TP, U$18.3
BOUT2_A4: TP36.TP, U$23.3
BOUT2_A5: TP44.TP, U$28.3
BOUT2_A6: TP52.TP, U$33.3
BOUT2_A7: TP60.TP, U$38.3
BOUT2_A8: TP68.TP, U$43.3
BOUT2_A9: TP76.TP, U$48.3
BOUT2_A10: TP84.TP, U$53.3
BOUT2_A11: TP92.TP, U$58.3
BOUT2_A12: TP100.TP, U$63.3
BOUT2_A13: TP108.TP, U$68.3
BOUT2_A14: TP116.TP, U$73.3
BOUT2_A15: TP124.TP, U$78.3
BOUT2_A16: TP132.TP, U$83.3
BOUT2_A17: TP140.TP, U$88.3
BOUT2_A18: TP148.TP, U$93.3
BOUT2_A19: TP156.TP, U$98.3
BOUT2_A20: TP164.TP, U$103.3
BOUT2_A21: TP172.TP, U$108.3
BOUT2_A22: TP180.TP, U$113.3
BOUT2_A23: TP188.TP, U$118.3
BOUT2_A24: TP196.TP, U$123.3
BOUT2_A25: TP204.TP, U$128.3
BOUT2_A26: TP212.TP, U$133.3
BOUT2_A27: TP220.TP, U$138.3
BOUT2_A28: TP228.TP, U$143.3
BOUT2_A29: TP236.TP, U$148.3
BOUT2_B: TP8.TP, U$16.3
BOUT2_B1: TP16.TP, U$7.3
BOUT2_B2: TP24.TP, U$13.3
BOUT2_B3: TP32.TP, U$19.3
BOUT2_B4: TP40.TP, U$24.3
BOUT2_B5: TP48.TP, U$29.3
BOUT2_B6: TP56.TP, U$34.3
BOUT2_B7: TP64.TP, U$39.3
BOUT2_B8: TP72.TP, U$44.3
BOUT2_B9: TP80.TP, U$49.3
BOUT2_B10: TP88.TP, U$54.3
BOUT2_B11: TP96.TP, U$59.3
BOUT2_B12: TP104.TP, U$64.3
BOUT2_B13: TP112.TP, U$69.3
BOUT2_B14: TP120.TP, U$74.3
BOUT2_B15: TP128.TP, U$79.3
BOUT2_B16: TP136.TP, U$84.3
BOUT2_B17: TP144.TP, U$89.3
BOUT2_B18: TP152.TP, U$94.3
BOUT2_B19: TP160.TP, U$99.3
BOUT2_B20: TP168.TP, U$104.3
BOUT2_B21: TP176.TP, U$109.3
BOUT2_B22: TP184.TP, U$114.3
BOUT2_B23: TP192.TP, U$119.3
BOUT2_B24: TP200.TP, U$124.3
BOUT2_B25: TP208.TP, U$129.3
BOUT2_B26: TP216.TP, U$134.3
BOUT2_B27: TP224.TP, U$139.3
BOUT2_B28: TP232.TP, U$144.3
BOUT2_B29: TP240.TP, U$149.3
GND: C1.2, C2.2, C3.2, C4.2, C5.2, U$1.8, U$1.18, U$1.27, U$1.35, U$1.45, U$1.53, U$1.62, U$1.72, U$5.2, U$5.4, U$11.1, U$11.4, U$11.11, U$11.T_PAD, U$16.1, U$16.4, U$16.11, U$16.T_PAD
GND1: C6.2, C7.2, C8.2, C9.2, C10.2, U$2.8, U$2.18, U$2.27, U$2.35, U$2.45, U$2.53, U$2.62, U$2.72, U$3.2, U$3.4, U$6.1, U$6.4, U$6.11, U$6.T_PAD, U$7.1, U$7.4, U$7.11, U$7.T_PAD
GND2: C11.2, C12.2, C13.2, C14.2, C15.2, U$9.8, U$9.18, U$9.27, U$9.35, U$9.45, U$9.53, U$9.62, U$9.72, U$10.2, U$10.4, U$12.1, U$12.4, U$12.11, U$12.T_PAD, U$13.1, U$13.4, U$13.11, U$13.T_PAD
GND3: C16.2, C17.2, C18.2, C19.2, C20.2, U$15.8, U$15.18, U$15.27, U$15.35, U$15.45, U$15.53, U$15.62, U$15.72, U$17.2, U$17.4, U$18.1, U$18.4, U$18.11, U$18.T_PAD, U$19.1, U$19.4, U$19.11, U$19.T_PAD
GND4: C21.2, C22.2, C23.2, C24.2, C25.2, U$21.8, U$21.18, U$21.27, U$21.35, U$21.45, U$21.53, U$21.62, U$21.72, U$22.2, U$22.4, U$23.1, U$23.4, U$23.11, U$23.T_PAD, U$24.1, U$24.4, U$24.11, U$24.T_PAD
GND5: C26.2, C27.2, C28.2, C29.2, C30.2, U$26.8, U$26.18, U$26.27, U$26.35, U$26.45, U$26.53, U$26.62, U$26.72, U$27.2, U$27.4, U$28.1, U$28.4, U$28.11, U$28.T_PAD, U$29.1, U$29.4, U$29.11, U$29.T_PAD
GND6: C31.2, C32.2, C33.2, C34.2, C35.2, U$31.8, U$31.18, U$31.27, U$31.35, U$31.45, U$31.53, U$31.62, U$31.72, U$32.2, U$32.4, U$33.1, U$33.4, U$33.11, U$33.T_PAD, U$34.1, U$34.4, U$34.11, U$34.T_PAD
GND7: C36.2, C37.2, C38.2, C39.2, C40.2, U$36.8, U$36.18, U$36.27, U$36.35, U$36.45, U$36.53, U$36.62, U$36.72, U$37.2, U$37.4, U$38.1, U$38.4, U$38.11, U$38.T_PAD, U$39.1, U$39.4, U$39.11, U$39.T_PAD
GND8: C41.2, C42.2, C43.2, C44.2, C45.2, U$41.8, U$41.18, U$41.27, U$41.35, U$41.45, U$41.53, U$41.62, U$41.72, U$42.2, U$42.4, U$43.1, U$43.4, U$43.11, U$43.T_PAD, U$44.1, U$44.4, U$44.11, U$44.T_PAD
GND9: C46.2, C47.2, C48.2, C49.2, C50.2, U$46.8, U$46.18, U$46.27, U$46.35, U$46.45, U$46.53, U$46.62, U$46.72, U$47.2, U$47.4, U$48.1, U$48.4, U$48.11, U$48.T_PAD, U$49.1, U$49.4, U$49.11, U$49.T_PAD
GND10: C51.2, C52.2, C53.2, C54.2, C55.2, U$51.8, U$51.18, U$51.27, U$51.35, U$51.45, U$51.53, U$51.62, U$51.72, U$52.2, U$52.4, U$53.1, U$53.4, U$53.11, U$53.T_PAD, U$54.1, U$54.4, U$54.11, U$54.T_PAD
GND11: C56.2, C57.2, C58.2, C59.2, C60.2, U$56.8, U$56.18, U$56.27, U$56.35, U$56.45, U$56.53, U$56.62, U$56.72, U$57.2, U$57.4, U$58.1, U$58.4, U$58.11, U$58.T_PAD, U$59.1, U$59.4, U$59.11, U$59.T_PAD
GND12: C61.2, C62.2, C63.2, C64.2, C65.2, U$61.8, U$61.18, U$61.27, U$61.35, U$61.45, U$61.53, U$61.62, U$61.72, U$62.2, U$62.4, U$63.1, U$63.4, U$63.11, U$63.T_PAD, U$64.1, U$64.4, U$64.11, U$64.T_PAD
GND13: C66.2, C67.2, C68.2, C69.2, C70.2, U$66.8, U$66.18, U$66.27, U$66.35, U$66.45, U$66.53, U$66.62, U$66.72, U$67.2, U$67.4, U$68.1, U$68.4, U$68.11, U$68.T_PAD, U$69.1, U$69.4, U$69.11, U$69.T_PAD
GND14: C71.2, C72.2, C73.2, C74.2, C75.2, U$71.8, U$71.18, U$71.27, U$71.35, U$71.45, U$71.53, U$71.62, U$71.72, U$72.2, U$72.4, U$73.1, U$73.4, U$73.11, U$73.T_PAD, U$74.1, U$74.4, U$74.11, U$74.T_PAD
GND15: C76.2, C77.2, C78.2, C79.2, C80.2, U$76.8, U$76.18, U$76.27, U$76.35, U$76.45, U$76.53, U$76.62, U$76.72, U$77.2, U$77.4, U$78.1, U$78.4, U$78.11, U$78.T_PAD, U$79.1, U$79.4, U$79.11, U$79.T_PAD
GND16: C81.2, C82.2, C83.2, C84.2, C85.2, U$81.8, U$81.18, U$81.27, U$81.35, U$81.45, U$81.53, U$81.62, U$81.72, U$82.2, U$82.4, U$83.1, U$83.4, U$83.11, U$83.T_PAD, U$84.1, U$84.4, U$84.11, U$84.T_PAD
GND17: C86.2, C87.2, C88.2, C89.2, C90.2, U$86.8, U$86.18, U$86.27, U$86.35, U$86.45, U$86.53, U$86.62, U$86.72, U$87.2, U$87.4, U$88.1, U$88.4, U$88.11, U$88.T_PAD, U$89.1, U$89.4, U$89.11, U$89.T_PAD
GND18: C91.2, C92.2, C93.2, C94.2, C95.2, U$91.8, U$91.18, U$91.27, U$91.35, U$91.45, U$91.53, U$91.62, U$91.72, U$92.2, U$92.4, U$93.1, U$93.4, U$93.11, U$93.T_PAD, U$94.1, U$94.4, U$94.11, U$94.T_PAD
GND19: C96.2, C97.2, C98.2, C99.2, C100.2, U$96.8, U$96.18, U$96.27, U$96.35, U$96.45, U$96.53, U$96.62, U$96.72, U$97.2, U$97.4, U$98.1, U$98.4, U$98.11, U$98.T_PAD, U$99.1, U$99.4, U$99.11, U$99.T_PAD
GND20: C101.2, C102.2, C103.2, C104.2, C105.2, U$101.8, U$101.18, U$101.27, U$101.35, U$101.45, U$101.53, U$101.62, U$101.72, U$102.2, U$102.4, U$103.1, U$103.4, U$103.11, U$103.T_PAD, U$104.1, U$104.4, U$104.11, U$104.T_PAD
GND21: C106.2, C107.2, C108.2, C109.2, C110.2, U$106.8, U$106.18, U$106.27, U$106.35, U$106.45, U$106.53, U$106.62, U$106.72, U$107.2, U$107.4, U$108.1, U$108.4, U$108.11, U$108.T_PAD, U$109.1, U$109.4, U$109.11, U$109.T_PAD
GND22: C111.2, C112.2, C113.2, C114.2, C115.2, U$111.8, U$111.18, U$111.27, U$111.35, U$111.45, U$111.53, U$111.62, U$111.72, U$112.2, U$112.4, U$113.1, U$113.4, U$113.11, U$113.T_PAD, U$114.1, U$114.4, U$114.11, U$114.T_PAD
GND23: C116.2, C117.2, C118.2, C119.2, C120.2, U$116.8, U$116.18, U$116.27, U$116.35, U$116.45, U$116.53, U$116.62, U$116.72, U$117.2, U$117.4, U$118.1, U$118.4, U$118.11, U$118.T_PAD, U$119.1, U$119.4, U$119.11, U$119.T_PAD
GND24: C121.2, C122.2, C123.2, C124.2, C125.2, U$121.8, U$121.18, U$121.27, U$121.35, U$121.45, U$121.53, U$121.62, U$121.72, U$122.2, U$122.4, U$123.1, U$123.4, U$123.11, U$123.T_PAD, U$124.1, U$124.4, U$124.11, U$124.T_PAD
GND25: C126.2, C127.2, C128.2, C129.2, C130.2, U$126.8, U$126.18, U$126.27, U$126.35, U$126.45, U$126.53, U$126.62, U$126.72, U$127.2, U$127.4, U$128.1, U$128.4, U$128.11, U$128.T_PAD, U$129.1, U$129.4, U$129.11, U$129.T_PAD
GND26: C131.2, C132.2, C133.2, C134.2, C135.2, U$131.8, U$131.18, U$131.27, U$131.35, U$131.45, U$131.53, U$131.62, U$131.72, U$132.2, U$132.4, U$133.1, U$133.4, U$133.11, U$133.T_PAD, U$134.1, U$134.4, U$134.11, U$134.T_PAD
GND27: C136.2, C137.2, C138.2, C139.2, C140.2, U$136.8, U$136.18, U$136.27, U$136.35, U$136.45, U$136.53, U$136.62, U$136.72, U$137.2, U$137.4, U$138.1, U$138.4, U$138.11, U$138.T_PAD, U$139.1, U$139.4, U$139.11, U$139.T_PAD
GND28: C141.2, C142.2, C143.2, C144.2, C145.2, U$141.8, U$141.18, U$141.27, U$141.35, U$141.45, U$141.53, U$141.62, U$141.72, U$142.2, U$142.4, U$143.1, U$143.4, U$143.11, U$143.T_PAD, U$144.1, U$144.4, U$144.11, U$144.T_PAD
GND29: C146.2, C147.2, C148.2, C149.2, C150.2, U$146.8, U$146.18, U$146.27, U$146.35, U$146.45, U$146.53, U$146.62, U$146.72, U$147.2, U$147.4, U$148.1, U$148.4, U$148.11, U$148.T_PAD, U$149.1, U$149.4, U$149.11, U$149.T_PAD
LIPO_IN: LIPO_IN.TP, U$4.L2
LIPO_IN1: LIPO_IN1.TP, U$8.L2
LIPO_IN2: LIPO_IN2.TP, U$14.L2
LIPO_IN3: LIPO_IN3.TP, U$20.L2
LIPO_IN4: LIPO_IN4.TP, U$25.L2
LIPO_IN5: LIPO_IN5.TP, U$30.L2
LIPO_IN6: LIPO_IN6.TP, U$35.L2
LIPO_IN7: LIPO_IN7.TP, U$40.L2
LIPO_IN8: LIPO_IN8.TP, U$45.L2
LIPO_IN9: LIPO_IN9.TP, U$50.L2
LIPO_IN10: LIPO_IN10.TP, U$55.L2
LIPO_IN11: LIPO_IN11.TP, U$60.L2
LIPO_IN12: LIPO_IN12.TP, U$65.L2
LIPO_IN13: LIPO_IN13.TP, U$70.L2
LIPO_IN14: LIPO_IN14.TP, U$75.L2
LIPO_IN15: LIPO_IN15.TP, U$80.L2
LIPO_IN16: LIPO_IN16.TP, U$85.L2
LIPO_IN17: LIPO_IN17.TP, U$90.L2
LIPO_IN18: LIPO_IN18.TP, U$95.L2
LIPO_IN19: LIPO_IN19.TP, U$100.L2
LIPO_IN20: LIPO_IN20.TP, U$105.L2
LIPO_IN21: LIPO_IN21.TP, U$110.L2
LIPO_IN22: LIPO_IN22.TP, U$115.L2
LIPO_IN23: LIPO_IN23.TP, U$120.L2
LIPO_IN24: LIPO_IN24.TP, U$125.L2
LIPO_IN25: LIPO_IN25.TP, U$130.L2
LIPO_IN26: LIPO_IN26.TP, U$135.L2
LIPO_IN27: LIPO_IN27.TP, U$140.L2
LIPO_IN28: LIPO_IN28.TP, U$145.L2
LIPO_IN29: LIPO_IN29.TP, U$150.L2
MOT_EN: U$1.5, U$1.32, U$1.50, U$1.59, U$11.15, U$16.15
MOT_EN1: U$2.5, U$2.32, U$2.50, U$2.59, U$6.15, U$7.15
MOT_EN2: U$9.5, U$9.32, U$9.50, U$9.59, U$12.15, U$13.15
MOT_EN3: U$15.5, U$15.32, U$15.50, U$15.59, U$18.15, U$19.15
MOT_EN4: U$21.5, U$21.32, U$21.50, U$21.59, U$23.15, U$24.15
MOT_EN5: U$26.5, U$26.32, U$26.50, U$26.59, U$28.15, U$29.15
MOT_EN6: U$31.5, U$31.32, U$31.50, U$31.59, U$33.15, U$34.15
MOT_EN7: U$36.5, U$36.32, U$36.50, U$36.59, U$38.15, U$39.15
MOT_EN8: U$41.5, U$41.32, U$41.50, U$41.59, U$43.15, U$44.15
MOT_EN9: U$46.5, U$46.32, U$46.50, U$46.59, U$48.15, U$49.15
MOT_EN10: U$51.5, U$51.32, U$51.50, U$51.59, U$53.15, U$54.15
MOT_EN11: U$56.5, U$56.32, U$56.50, U$56.59, U$58.15, U$59.15
MOT_EN12: U$61.5, U$61.32, U$61.50, U$61.59, U$63.15, U$64.15
MOT_EN13: U$66.5, U$66.32, U$66.50, U$66.59, U$68.15, U$69.15
MOT_EN14: U$71.5, U$71.32, U$71.50, U$71.59, U$73.15, U$74.15
MOT_EN15: U$76.5, U$76.32, U$76.50, U$76.59, U$78.15, U$79.15
MOT_EN16: U$81.5, U$81.32, U$81.50, U$81.59, U$83.15, U$84.15
MOT_EN17: U$86.5, U$86.32, U$86.50, U$86.59, U$88.15, U$89.15
MOT_EN18: U$91.5, U$91.32, U$91.50, U$91.59, U$93.15, U$94.15
MOT_EN19: U$96.5, U$96.32, U$96.50, U$96.59, U$98.15, U$99.15
MOT_EN20: U$101.5, U$101.32, U$101.50, U$101.59, U$103.15, U$104.15
MOT_EN21: U$106.5, U$106.32, U$106.50, U$106.59, U$108.15, U$109.15
MOT_EN22: U$111.5, U$111.32, U$111.50, U$111.59, U$113.15, U$114.15
MOT_EN23: U$116.5, U$116.32, U$116.50, U$116.59, U$118.15, U$119.15
MOT_EN24: U$121.5, U$121.32, U$121.50, U$121.59, U$123.15, U$124.15
MOT_EN25: U$126.5, U$126.32, U$126.50, U$126.59, U$128.15, U$129.15
MOT_EN26: U$131.5, U$131.32, U$131.50, U$131.59, U$133.15, U$134.15
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
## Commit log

2019-01-27 PCB created on day 1 of project
2019-01-28 PCB panel created and sent to PCBWay for review
2019-01-28 Added PCB panel rendered images
2019-02-08 PCB first order placed, cleared PCB panel files. ESP and Python Controller software written
2019-02-10 ESP Code updated to accept directional commands. TODO Servo interfacing
